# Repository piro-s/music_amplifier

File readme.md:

# Music amplifier:  
A simple two-channel amplifier on a chip TDA7851L.  

## scheme:  
### scheme_v2.1:  
[pdf](docs/music_amplifier_v2.1.pdf)  

## gerber:  
Archive for production:  
[gerber_2.1](https://github.com/piro-s/music_amplifier/raw/main/gerber/music_amplifier_v2.1.zip)

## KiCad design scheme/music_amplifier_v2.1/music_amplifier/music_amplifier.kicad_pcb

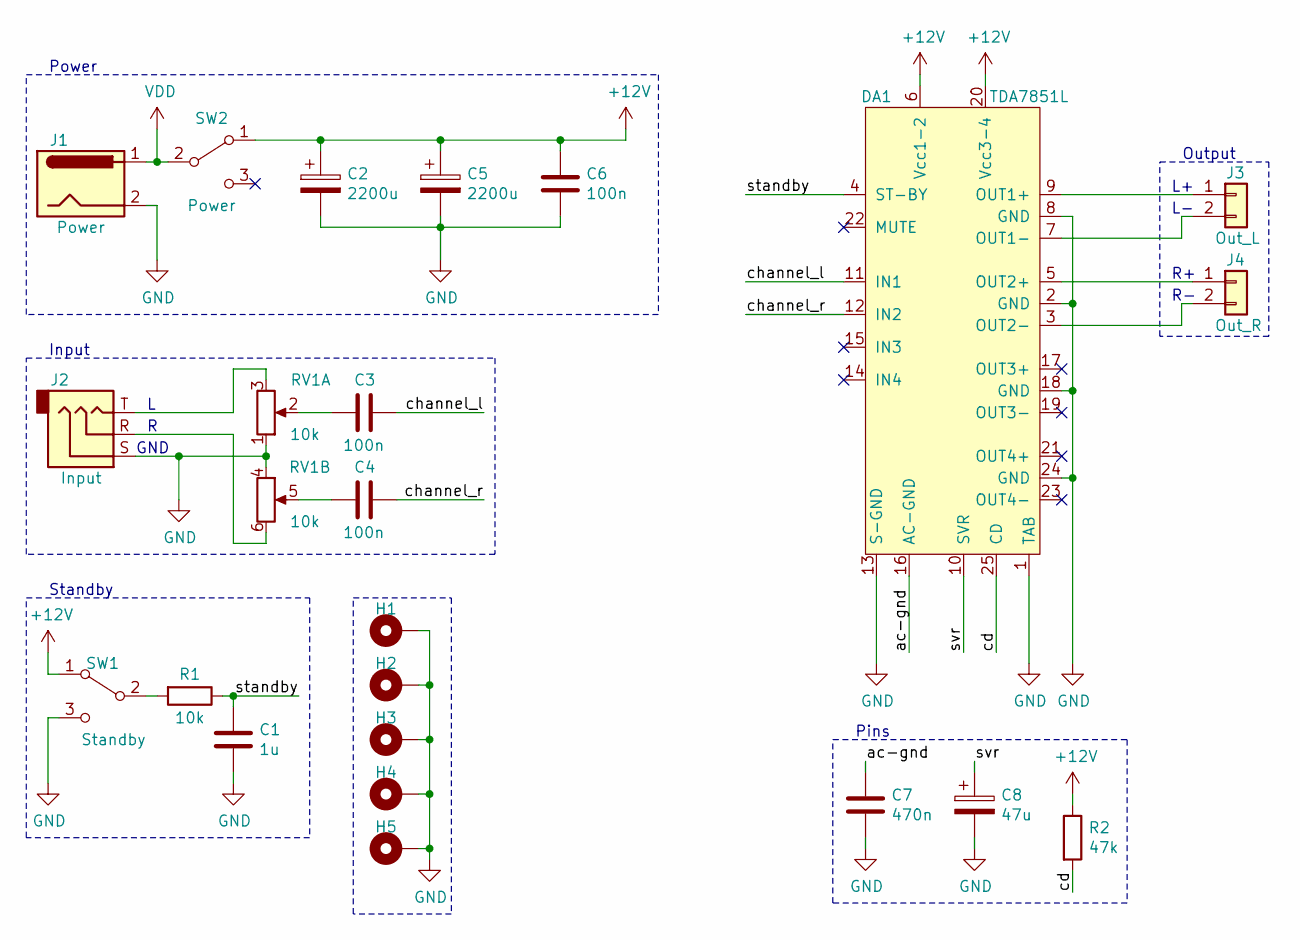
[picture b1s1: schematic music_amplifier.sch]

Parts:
C1: 1u; C_1206_3216Metric_Pad1.33x1.80mm_HandSolder
C2, C5: 2200u; CP_Radial_D13.0mm_P5.00mm
C3, C4, C6: 100n; C_0603_1608Metric_Pad1.08x0.95mm_HandSolder
C7: 470n; C_0603_1608Metric_Pad1.08x0.95mm_HandSolder
C8: 47u; CP_Radial_D5.0mm_P2.50mm
DA1: TDA7851L; flexiwatt25
H1, H2, H3, H4, H5: GND; MountingHole_3.2mm_M3
J1: Power; BarrelJack_Wuerth_6941xx301002
J2: Input; Jack_3.5mm_PJ322
J3: Out_L; PinSocket_1x02_P2.54mm_Vertical
J4: Out_R; PinSocket_1x02_P2.54mm_Vertical
R1: 10k; R_0603_1608Metric_Pad0.98x0.95mm_HandSolder
R2: 47k; R_0603_1608Metric_Pad0.98x0.95mm_HandSolder
RV1: 10k; Potentiometer_Alps_RK163_Dual_Horizontal
SW1: Standby; MTS-102-C4
SW2: Power; MTS-102-C4

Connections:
+12V: C2.1, C5.1, C6.1, DA1.6 (Vcc1-2), DA1.20 (Vcc3-4), R2.1, SW1.1 (A), SW2.1 (A)
/ac-gnd: C7.1, DA1.16 (AC-GND)
/cd: DA1.25 (CD), R2.2
/channel_l: C3.1, DA1.11 (IN1)
/channel_r: C4.1, DA1.12 (IN2)
/standby: C1.1, DA1.4 (ST-BY), R1.1
/svr: C8.1, DA1.10 (SVR)
GND: C1.2, C2.2, C5.2, C6.2, C7.2, C8.2, DA1.1 (TAB), DA1.2 (GND), DA1.8 (GND), DA1.13 (S-GND), DA1.18 (GND), DA1.24 (GND), H1.1, H2.1, H3.1, H4.1, H5.1, J1.2, J2.S, RV1.1, RV1.4, SW1.3 (C)
unnamed: C3.2, RV1.2
unnamed: C4.2, RV1.5
unnamed: DA1.3 (OUT2-), J4.2
unnamed: DA1.5 (OUT2+), J4.1
unnamed: DA1.7 (OUT1-), J3.2
unnamed: DA1.9 (OUT1+), J3.1
unnamed: J2.R, RV1.6
unnamed: J2.T, RV1.3
unnamed: R1.2, SW1.2 (B)
VDD: J1.1, SW2.2 (B)

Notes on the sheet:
GND
Power
Input
Standby
Pins
Output

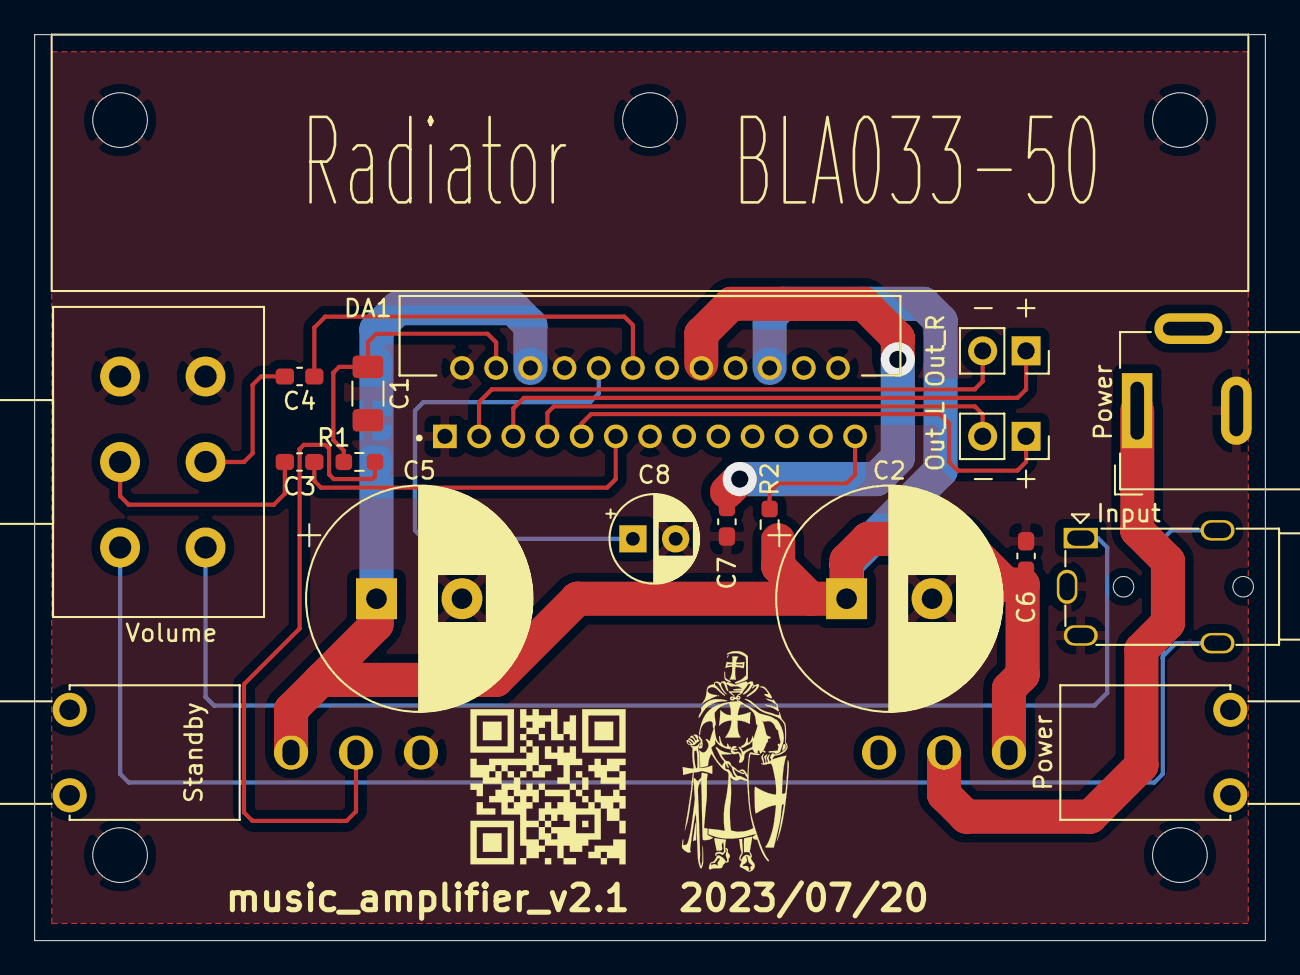
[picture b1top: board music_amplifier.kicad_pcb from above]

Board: 2 copper layers, 72.0 x 53.0 mm, 23 parts (0 on the bottom side), 18 nets.

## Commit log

2023-07-30 Initial
    A simple two-channel amplifier on a chip TDA7851L.
2023-07-30 fix: Gerber link
    Fixed link to gerber archive (leading to another
    repository).
2023-07-30 small: Gitignore
